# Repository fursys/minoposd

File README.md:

minimOSD clone for using with LibrePilot (Open Pilot) flight controllers.

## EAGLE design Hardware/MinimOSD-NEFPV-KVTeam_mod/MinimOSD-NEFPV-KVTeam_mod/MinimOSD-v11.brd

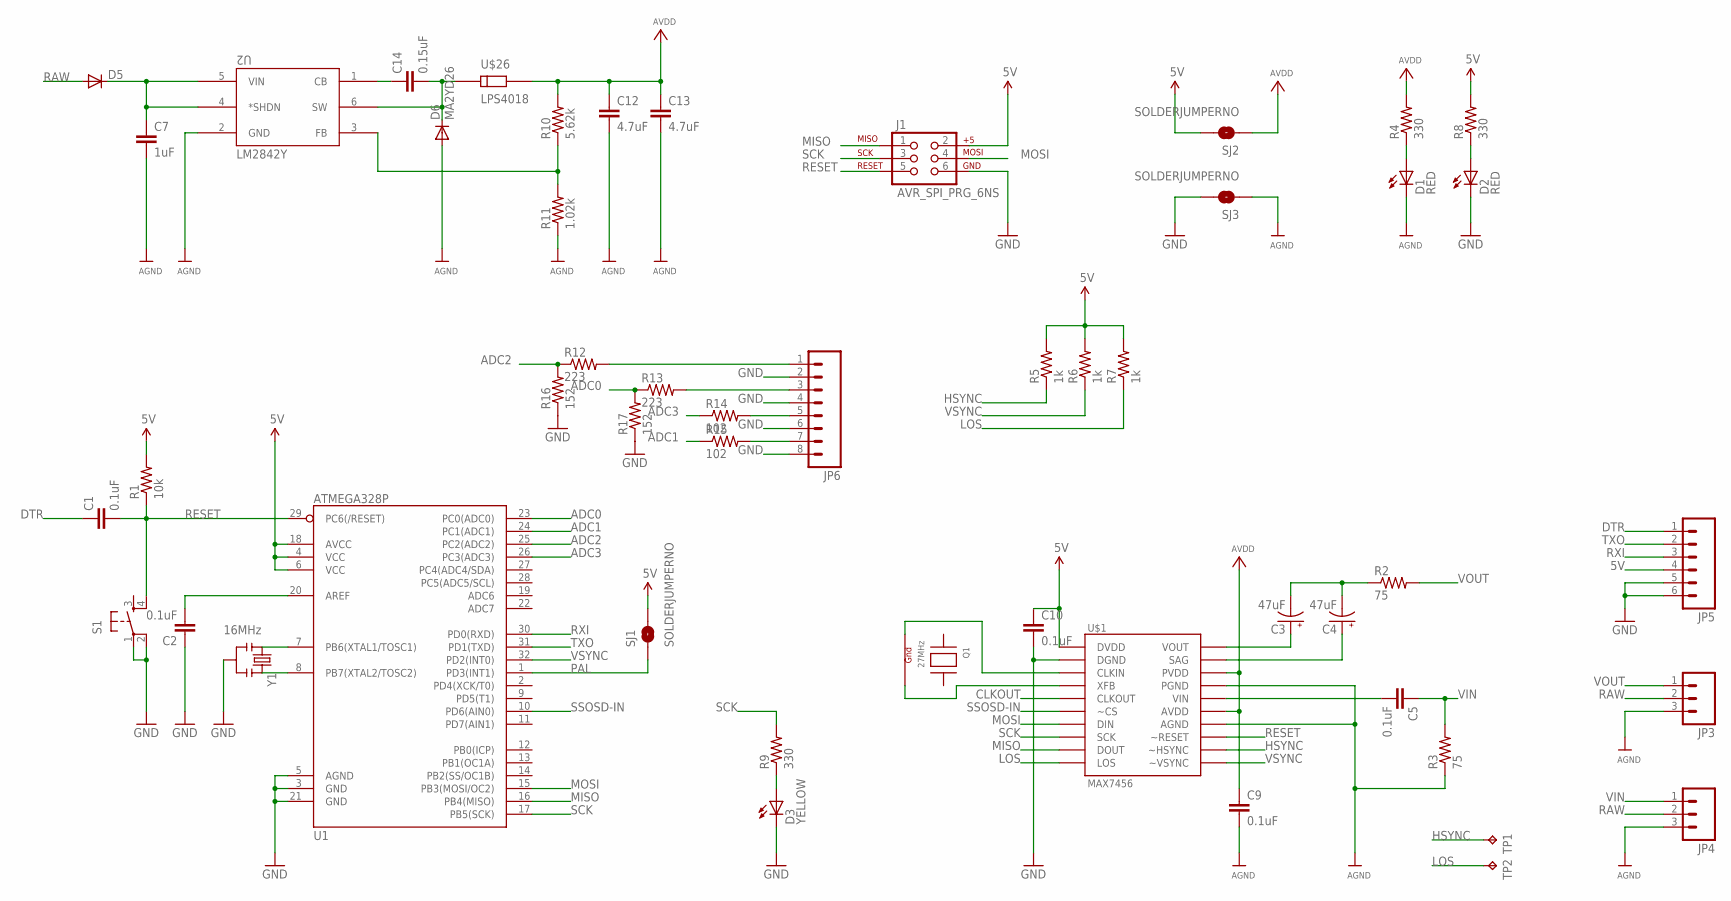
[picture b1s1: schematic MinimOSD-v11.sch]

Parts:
C1, C2, C5, C9, C10: 0.1uF; 0402-CAP
C3, C4: 47uF; EIA3528
C7: 1uF; 0805
C12, C13: 4.7uF; 0805
C14: 0.15uF; 0402-CAP
D1, D2: RED; LED-0603
D3: YELLOW; LED-0603
D5: DIODE-SOD123; SOD123
D6: MA2YD26; SOD123
J1: AVR_SPI_PRG_6NS; 2X3-NS
JP3, JP4: M03PTH; 1X03
JP5: M06SIP; 1X06
JP6: M081X08; 1X08
Q1: 27MHz; NX3225
R1: 10k; 0402-RES
R2, R3: 75; 0402-RES
R4, R8, R9: 330; 0402-RES
R5, R6, R7: 1k; 0402-RES
R10: 5.62k; 0402-RES
R11: 1.02k; 0402-RES
R12, R13: 223; 0402-RES
R14, R15: 102; 0402-RES
R16, R17: 152; 0402-RES
S1: TAC_SWITCHSMD; TACTILE_SWITCH_SMD
SJ1, SJ2, SJ3: SOLDERJUMPERNO; SJ_2S-NO
TP1, TP2: TPTP12SQ; TP12SQ
U1: ATMEGA328P; TQFP32-08
U2: LM2842Y; MK06A
U$1: MAX7456; TSSOP28
U$26: LPS4018
Y1: 16MHz; RESONATOR-SMD

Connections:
5V: C10.1, J1.2, JP5.4, R1.2, R5.2, R6.2, R7.2, R8.2, SJ1.2, SJ2.2, U1.4 (VCC), U1.6 (VCC), U1.18 (AVCC), U$1.3 (DVDD)
ADC0: R13.1, R17.2, U1.23 (PC0(ADC0))
ADC1: R15.1, U1.24 (PC1(ADC1))
ADC2: R12.1, R16.2, U1.25 (PC2(ADC2))
ADC3: R14.1, U1.26 (PC3(ADC3))
AGND: C7.2, C9.2, C12.2, C13.2, D1.C, D6.A, JP3.3, JP4.3, R3.1, R11.1, SJ3.1, U2.2 (GND), U$1.20 (AGND), U$1.23 (PGND)
AVDD: C9.1, C12.1, C13.1, R4.2, R10.2, SJ2.1, U$1.21 (AVDD), U$1.24 (PVDD), U$26.B
CLKOUT: U$1.7 (CLKOUT)
DTR: C1.1, JP5.1
GND: C2.1, C10.2, D2.C, D3.C, J1.6, JP5.5, JP5.6, JP6.2, JP6.4, JP6.6, JP6.8, R16.1, R17.1, S1.1, S1.2, SJ3.2, U1.3 (GND), U1.5 (AGND), U1.21 (GND), U$1.4 (DGND), Y1.2
HSYNC: R5.1, TP1.TP, U$1.18 (~HSYNC)
LOS: R7.1, TP2.TP, U$1.12 (LOS)
MISO: J1.1, U1.16 (PB4(MISO)), U$1.11 (DOUT)
MOSI: J1.4, U1.15 (PB3(MOSI/OC2)), U$1.9 (DIN)
unnamed: Q1.4 (G2), U$1.6 (XFB)
unnamed: C2.2, U1.20 (AREF)
unnamed: U1.7 (PB6(XTAL1/TOSC1)), Y1.1
unnamed: U1.8 (PB7(XTAL2/TOSC2)), Y1.3
unnamed: Q1.2 (G1), U$1.5 (CLKIN)
unnamed: C3.A (+), U$1.26 (VOUT)
unnamed: C4.A (+), U$1.25 (SAG)
unnamed: C3.C (-), C4.C (-), R2.1
unnamed: C5.2, U$1.22 (VIN)
unnamed: D1.A, R4.1
unnamed: D2.A, R8.1
unnamed: D3.A, R9.1
unnamed: C7.1, D5.C, U2.4 (*SHDN), U2.5 (VIN)
unnamed: C14.1, U2.1 (CB)
unnamed: C14.2, D6.C, U2.6 (SW), U$26.A
unnamed: JP6.7, R15.2
unnamed: R10.1, R11.2, U2.3 (FB)
unnamed: JP6.5, R14.2
unnamed: JP6.3, R13.2
unnamed: JP6.1, R12.2
PAL: SJ1.1, U1.1 (PD3(INT1))
RAW: D5.A, JP3.2, JP4.2
RESET: C1.2, J1.5, R1.1, S1.4, U1.29 (PC6(/RESET)), U$1.19 (~RESET)
RXI: JP5.3, U1.30 (PD0(RXD))
SCK: J1.3, R9.2, U1.17 (PB5(SCK)), U$1.10 (SCK)
SSOSD-IN: U1.10 (PD6(AIN0)), U$1.8 (~CS)
TXO: JP5.2, U1.31 (PD1(TXD))
VIN: C5.1, JP4.1, R3.2
VOUT: JP3.1, R2.2
VSYNC: R6.1, U1.32 (PD2(INT0)), U$1.17 (~VSYNC)

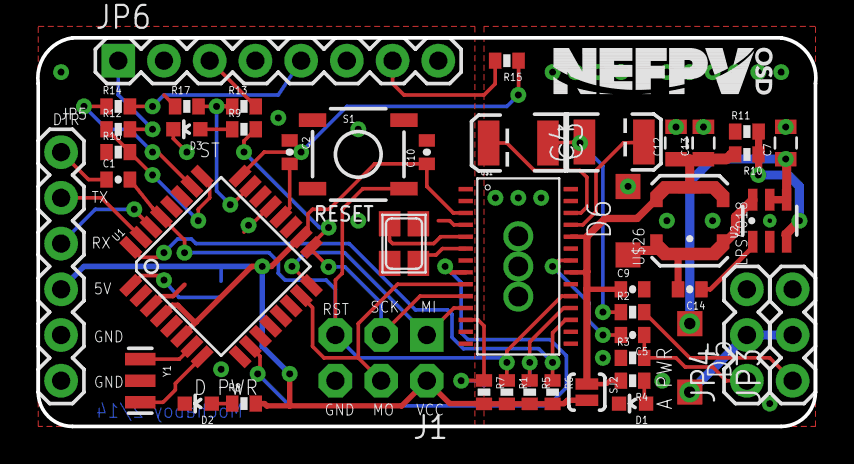
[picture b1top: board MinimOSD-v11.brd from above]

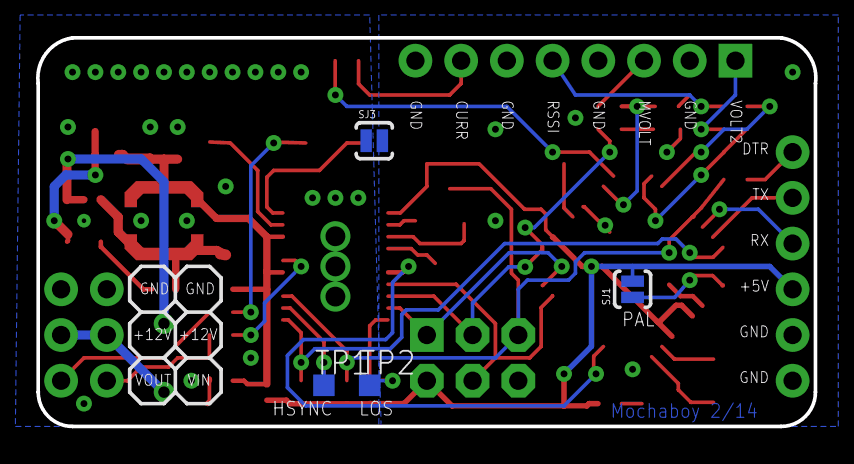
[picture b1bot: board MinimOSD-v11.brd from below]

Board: 4 copper layers, 43.2 x 21.6 mm, 50 parts (4 on the bottom side), 43 nets.

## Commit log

2016-05-04 initialization
2016-05-04 readme inserted
2016-08-07 Analog Rssi port was changet from 1 to 3

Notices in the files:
parts and their libraries:
SparkFun-Connectors: Licensing: Creative Commons ShareAlike 4.0 International - https://creativecommons.org/licenses/by-sa/4.0
